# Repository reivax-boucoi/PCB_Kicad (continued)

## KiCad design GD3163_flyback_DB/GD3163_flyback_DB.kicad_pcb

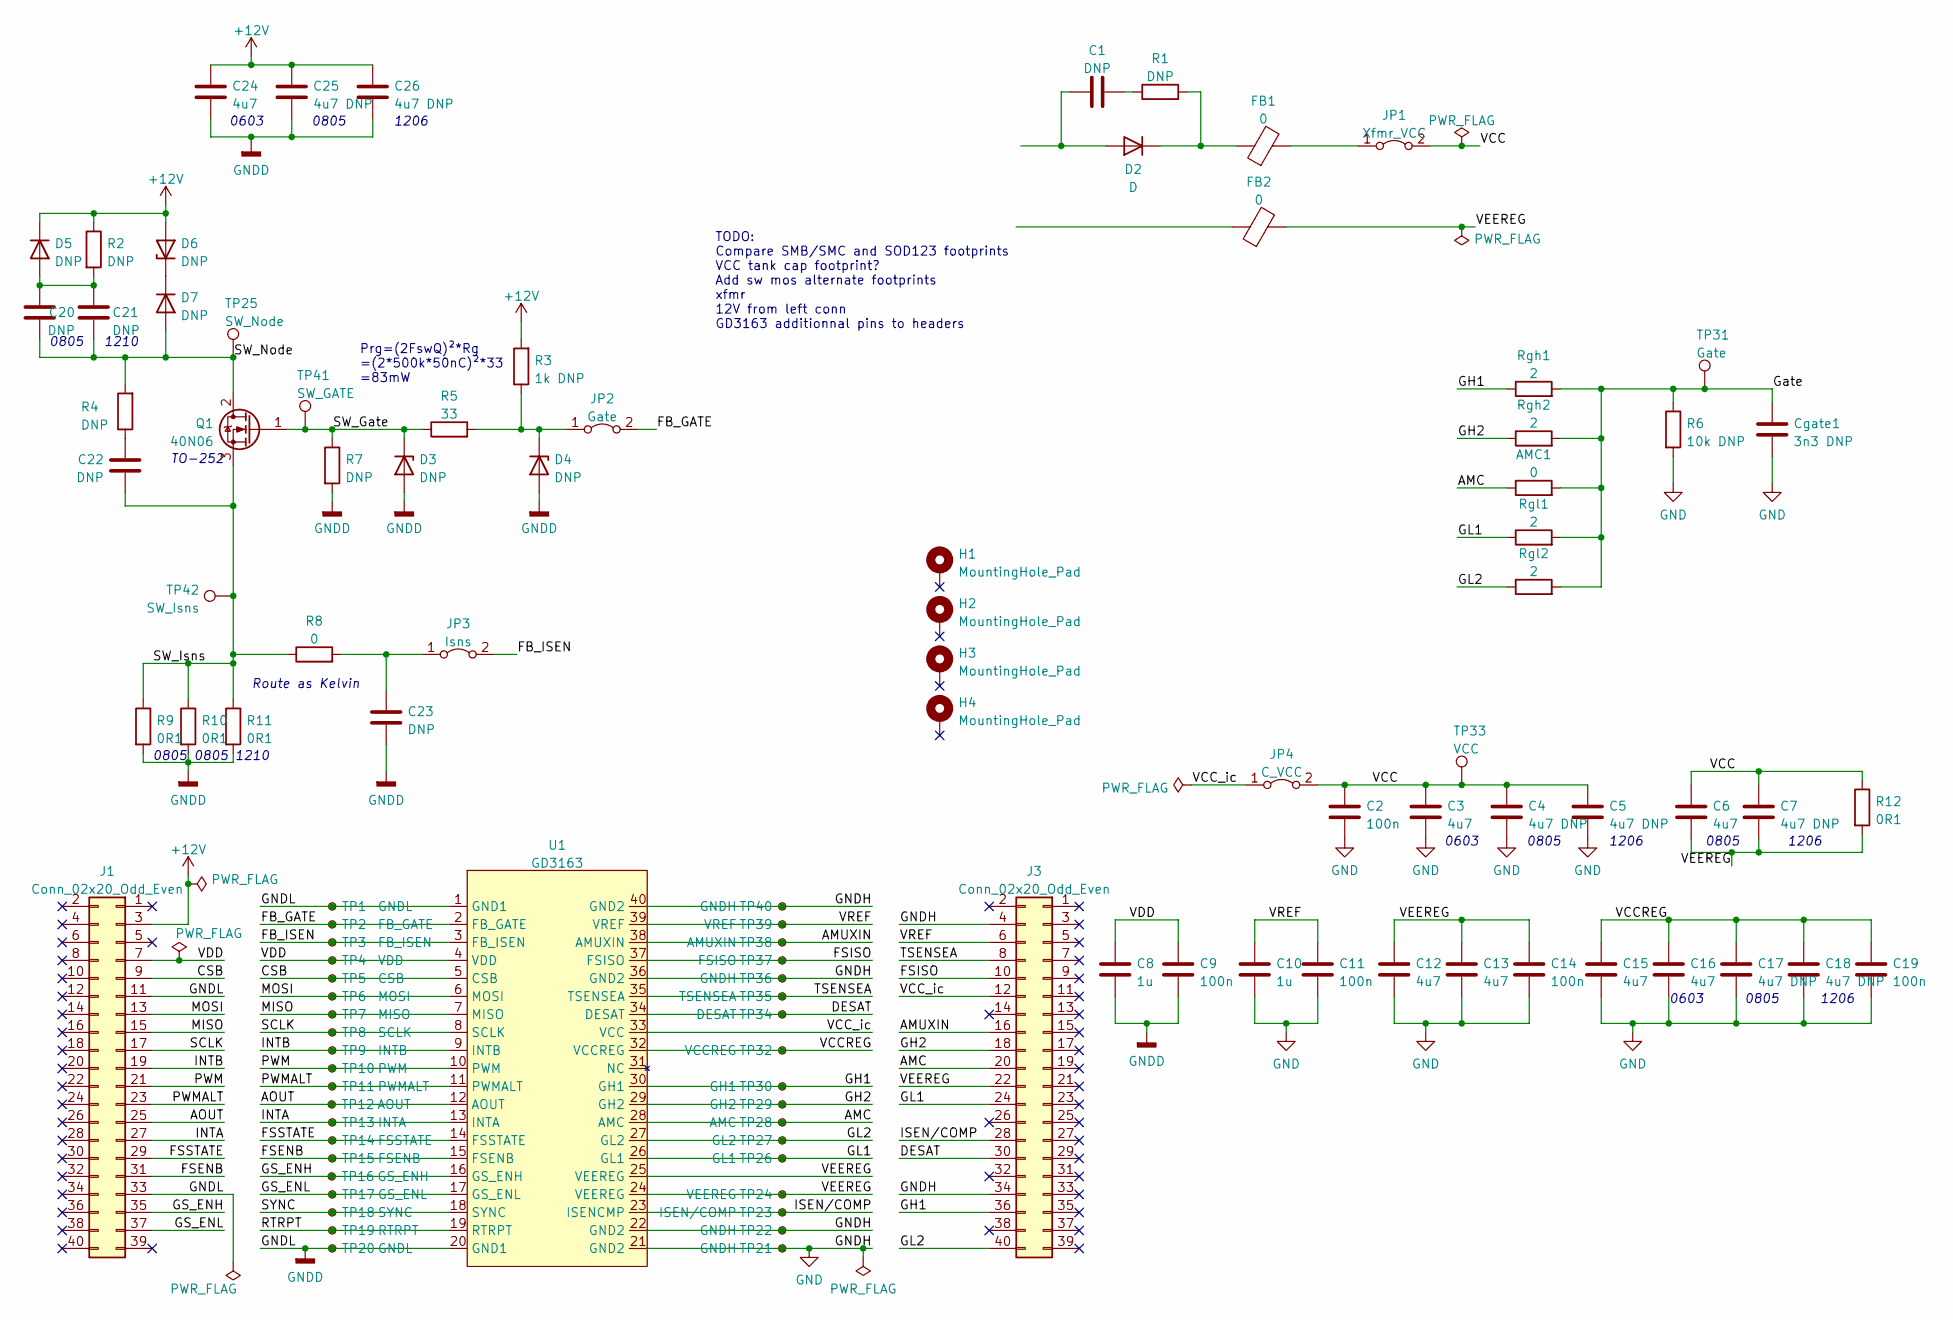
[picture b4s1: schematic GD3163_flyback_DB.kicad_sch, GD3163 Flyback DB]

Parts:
AMC1: 0; R_1206_3216Metric_Pad1.30x1.75mm_HandSolder
C1, C20, C22: DNP; C_0805_2012Metric_Pad1.18x1.45mm_HandSolder
C2, C9, C11, C14, C19: 100n; C_0603_1608Metric_Pad1.08x0.95mm_HandSolder
C3, C6, C12, C13, C15, C16, C24: 4u7; C_0603_1608Metric_Pad1.08x0.95mm_HandSolder
C4, C17, C25: 4u7 DNP; C_0805_2012Metric_Pad1.18x1.45mm_HandSolder
C5, C7, C18, C26: 4u7 DNP; C_1206_3216Metric_Pad1.33x1.80mm_HandSolder
C8, C10: 1u; C_0603_1608Metric_Pad1.08x0.95mm_HandSolder
C21: DNP; C_1210_3225Metric
C23: DNP; C_0603_1608Metric_Pad1.08x0.95mm_HandSolder
Cgate1: 3n3 DNP; C_0805_2012Metric_Pad1.18x1.45mm_HandSolder
D2: D; D_SMA-SMB_Universal_Handsoldering
D3, D4: DNP; D_SOD-323_HandSoldering
D5, D6, D7: DNP; D_SMA-SMB_Universal_Handsoldering
FB1, FB2: 0; L_0805_2012Metric_Pad1.05x1.20mm_HandSolder
H1, H2, H3, H4: MountingHole_Pad; MountingHole_4.3mm_M4_Pad_Via
J1, J3: Conn_02x20_Odd_Even; PinHeader_2x20_P2.54mm_Vertical
JP1: Xfmr_VCC; PinHeader_1x02_P2.54mm_Vertical
JP2: Gate; PinHeader_1x02_P2.54mm_Vertical
JP3: Isns; PinHeader_1x02_P2.54mm_Vertical
JP4: C_VCC; PinHeader_1x02_P2.54mm_Vertical
Q1: 40N06; TO-252-2
R1, R7: DNP; R_0805_2012Metric_Pad1.20x1.40mm_HandSolder
R2: DNP; R_1210_3225Metric_Pad1.30x2.65mm_HandSolder
R3: 1k DNP; R_0805_2012Metric_Pad1.20x1.40mm_HandSolder
R4: DNP; R_1206_3216Metric_Pad1.30x1.75mm_HandSolder
R5: 33; R_0805_2012Metric_Pad1.20x1.40mm_HandSolder
R6: 10k DNP; R_0805_2012Metric_Pad1.20x1.40mm_HandSolder
R8: 0; R_0805_2012Metric_Pad1.20x1.40mm_HandSolder
R9, R10: 0R1; R_0805_2012Metric_Pad1.20x1.40mm_HandSolder
R11: 0R1; R_1210_3225Metric_Pad1.30x2.65mm_HandSolder
R12: 0R1; R_SocketINSA_L6.3mm_D2.5mm_P10.16mm_Horizontal
Rgh1, Rgh2: 2; R_1206_3216Metric_Pad1.30x1.75mm_HandSolder
Rgl1, Rgl2: 2; R_1206_3216Metric_Pad1.30x1.75mm_HandSolder
TP1, TP20: GNDL; TestPoint_Keystone_5010-5014_Multipurpose
TP2: FB_GATE; TestPoint_Keystone_5010-5014_Multipurpose
TP3: FB_ISEN; TestPoint_Keystone_5010-5014_Multipurpose
TP4: VDD; TestPoint_Keystone_5010-5014_Multipurpose
TP5: CSB; TestPoint_Keystone_5010-5014_Multipurpose
TP6: MOSI; TestPoint_Keystone_5010-5014_Multipurpose
TP7: MISO; TestPoint_Keystone_5010-5014_Multipurpose
TP8: SCLK; TestPoint_Keystone_5010-5014_Multipurpose
TP9: INTB; TestPoint_Keystone_5010-5014_Multipurpose
TP10: PWM; TestPoint_Keystone_5010-5014_Multipurpose
TP11: PWMALT; TestPoint_Keystone_5010-5014_Multipurpose
TP12: AOUT; TestPoint_Keystone_5010-5014_Multipurpose
TP13: INTA; TestPoint_Keystone_5010-5014_Multipurpose
TP14: FSSTATE; TestPoint_Keystone_5010-5014_Multipurpose
TP15: FSENB; TestPoint_Keystone_5010-5014_Multipurpose
TP16: GS_ENH; TestPoint_Keystone_5010-5014_Multipurpose
TP17: GS_ENL; TestPoint_Keystone_5010-5014_Multipurpose
TP18: SYNC; TestPoint_Keystone_5010-5014_Multipurpose
TP19: RTRPT; TestPoint_Keystone_5010-5014_Multipurpose
TP21, TP22, TP36, TP40: GNDH; TestPoint_Keystone_5010-5014_Multipurpose
TP23: ISEN/COMP; TestPoint_Keystone_5010-5014_Multipurpose
TP24: VEEREG; TestPoint_Keystone_5010-5014_Multipurpose
TP25: SW_Node; TestPoint_Keystone_5010-5014_Multipurpose
TP26: GL1; TestPoint_Keystone_5010-5014_Multipurpose
TP27: GL2; TestPoint_Keystone_5010-5014_Multipurpose
TP28: AMC; TestPoint_Keystone_5010-5014_Multipurpose
TP29: GH2; TestPoint_Keystone_5010-5014_Multipurpose
TP30: GH1; TestPoint_Keystone_5010-5014_Multipurpose
TP31: Gate; TestPoint_Keystone_5010-5014_Multipurpose
TP32: VCCREG; TestPoint_Keystone_5010-5014_Multipurpose
TP33: VCC; TestPoint_Keystone_5010-5014_Multipurpose
TP34: DESAT; TestPoint_Keystone_5010-5014_Multipurpose
TP35: TSENSEA; TestPoint_Keystone_5010-5014_Multipurpose
TP37: FSISO; TestPoint_Keystone_5010-5014_Multipurpose
TP38: AMUXIN; TestPoint_Keystone_5010-5014_Multipurpose
TP39: VREF; TestPoint_Keystone_5010-5014_Multipurpose
TP41: SW_GATE; TestPoint_Keystone_5010-5014_Multipurpose
TP42: SW_Isns; TestPoint_Keystone_5010-5014_Multipurpose
U1: GD3163; GD3163_SOIC-40_1.575x0.3, 9.575w

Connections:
+12V: C24.1, C25.1, C26.1, D5.1 (K), D6.2 (A), J1.3, R2.1, R3.2
/AMC: AMC1.1, J3.20, TP28.1, U1.28 (AMC)
/AMUXIN: J3.16, TP38.1, U1.38 (AMUXIN)
/AOUT: J1.25, TP12.1, U1.12 (AOUT)
/CSB: J1.9, TP5.1, U1.5 (CSB)
/DESAT: J3.30, TP34.1, U1.34 (DESAT)
/FB_GATE: JP2.2 (B), TP2.1, U1.2 (FB_GATE)
/FB_ISEN: JP3.2 (B), TP3.1, U1.3 (FB_ISEN)
/FSENB: J1.31, TP15.1, U1.15 (FSENB)
/FSISO: J3.10, TP37.1, U1.37 (FSISO)
/FSSTATE: J1.29, TP14.1, U1.14 (FSSTATE)
/GH1: J3.36, Rgh1.1, TP30.1, U1.30 (GH1)
/GH2: J3.18, Rgh2.1, TP29.1, U1.29 (GH2)
/GL1: J3.24, Rgl1.1, TP26.1, U1.26 (GL1)
/GL2: J3.40, Rgl2.1, TP27.1, U1.27 (GL2)
/GS_ENH: J1.35, TP16.1, U1.16 (GS_ENH)
/GS_ENL: J1.37, TP17.1, U1.17 (GS_ENL)
/Gate: AMC1.2, Cgate1.1, R6.1, Rgh1.2, Rgh2.2, Rgl1.2, Rgl2.2, TP31.1
/INTA: J1.27, TP13.1, U1.13 (INTA)
/INTB: J1.19, TP9.1, U1.9 (INTB)
/ISEN/COMP: J3.28, TP23.1, U1.23 (ISENCMP)
/MISO: J1.15, TP7.1, U1.7 (MISO)
/MOSI: J1.13, TP6.1, U1.6 (MOSI)
/PWM: J1.21, TP10.1, U1.10 (PWM)
/PWMALT: J1.23, TP11.1, U1.11 (PWMALT)
/RTRPT: TP19.1, U1.19 (RTRPT)
/SCLK: J1.17, TP8.1, U1.8 (SCLK)
/SW_Gate: D3.1 (K), Q1.1 (G), R5.1, R7.1, TP41.1
/SW_Isns: C22.2, Q1.3 (S), R8.1, R9.1, R10.1, R11.1, TP42.1
/SW_Node: C20.2, C21.2, D7.2 (A), Q1.2 (D), R4.2, TP25.1
/SYNC: TP18.1, U1.18 (SYNC)
/TSENSEA: J3.8, TP35.1, U1.35 (TSENSEA)
/VCC: C2.1, C3.1, C4.1, C5.1, C6.1, C7.1, JP1.2 (B), JP4.2 (B), R12.1, TP33.1
/VCCREG: C15.1, C16.1, C17.1, C18.1, C19.1, TP32.1, U1.32 (VCCREG)
/VCC_ic: J3.12, JP4.1 (A), U1.33 (VCC)
/VDD: C8.1, C9.1, J1.7, TP4.1, U1.4 (VDD)
/VEEREG: C6.2, C7.2, C12.1, C13.1, C14.1, FB2.2, J3.22, R12.2, TP24.1, U1.24 (VEEREG), U1.25 (VEEREG)
/VREF: C10.1, C11.1, J3.6, TP39.1, U1.39 (VREF)
GND: C2.2, C3.2, C4.2, C5.2, C10.2, C11.2, C12.2, C13.2, C14.2, C15.2, C16.2, C17.2, C18.2, C19.2, Cgate1.2, J3.4, J3.34, R6.2, TP21.1, TP22.1, TP36.1, TP40.1, U1.21 (GND2), U1.22 (GND2), U1.36 (GND2), U1.40 (GND2)
GNDD: C8.2, C9.2, C23.2, C24.2, C25.2, C26.2, D3.2 (A), D4.2 (A), J1.11, J1.33, R7.2, R9.2, R10.2, R11.2, TP1.1, TP20.1, U1.1 (GND1), U1.20 (GND1)
unnamed: C1.1, D2.2 (A)
unnamed: C1.2, R1.1
unnamed: C20.1, C21.1, D5.2 (A), R2.2
unnamed: C22.1, R4.1
unnamed: C23.1, JP3.1 (A), R8.2
unnamed: D2.1 (K), FB1.1, R1.2
unnamed: D4.1 (K), JP2.1 (A), R3.1, R5.2
unnamed: D6.1 (K), D7.1 (K)
unnamed: FB1.2, JP1.1 (A)

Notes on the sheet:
0805 1210
0805 1206
0603 0805 1206
0805 0805 1210
TO-252
TODO: Compare SMB/SMC and SOD123 footprints VCC tank cap footprint? Add sw mos alternate footprints xfmr 12V from left conn GD3163 additionnal pins to headers
0603 0805 1206
Prg=(2FswQ)²*Rg =(2*500k*50nC)²*33 =83mW
Route as Kelvin

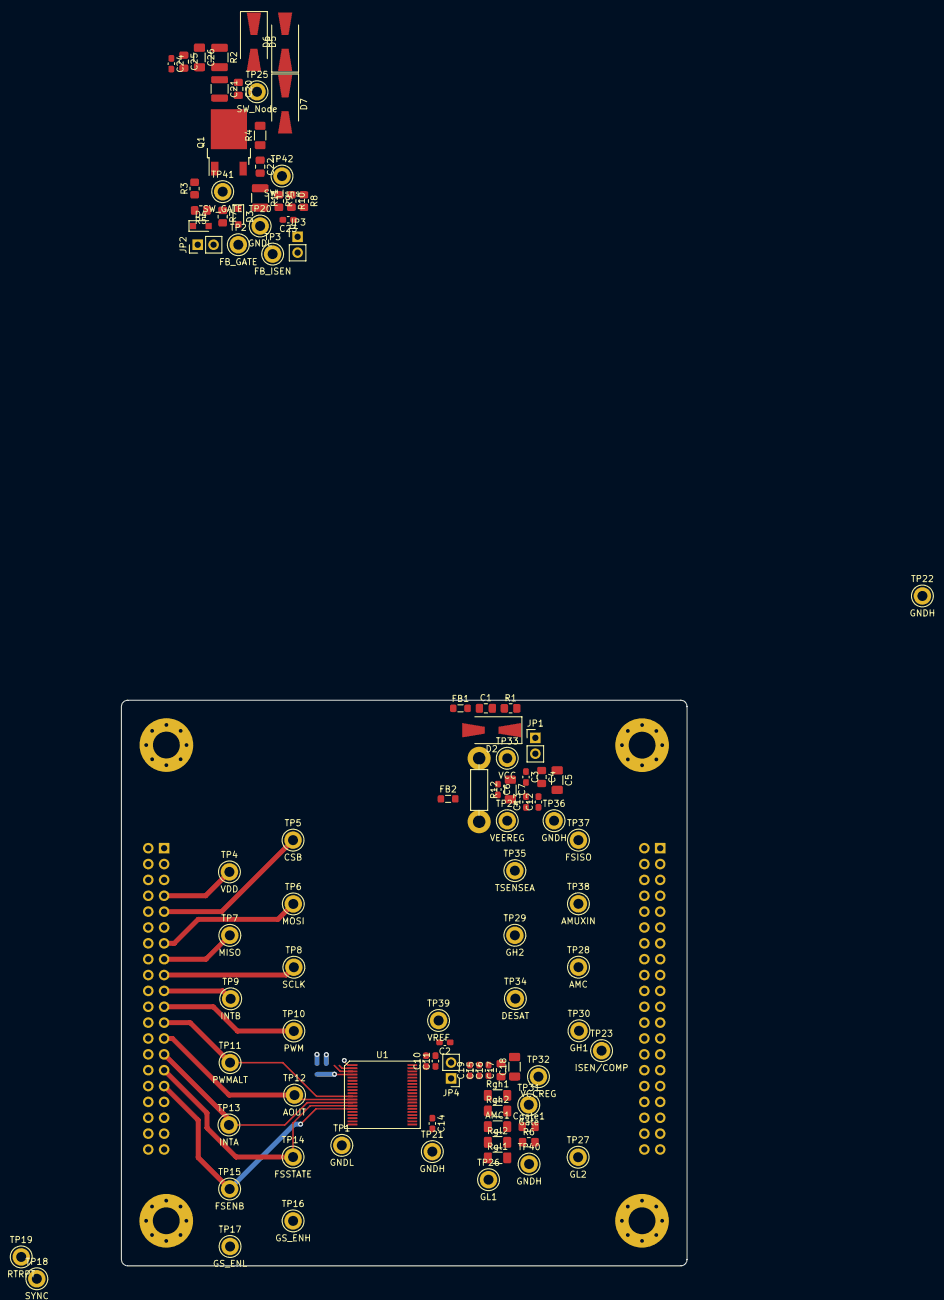
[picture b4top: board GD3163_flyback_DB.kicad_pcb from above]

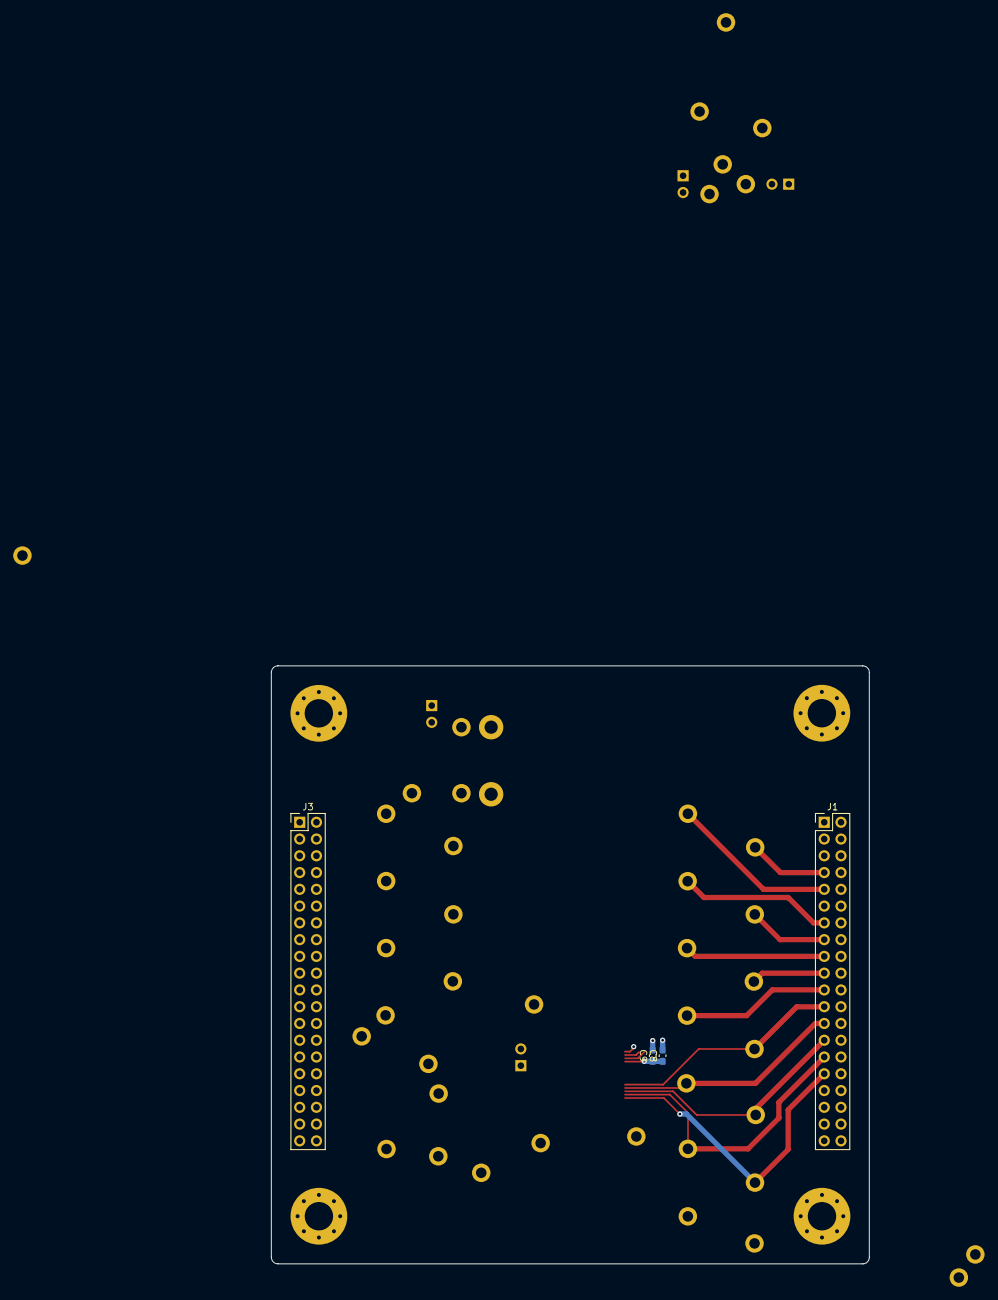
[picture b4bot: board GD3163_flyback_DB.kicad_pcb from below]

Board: 4 copper layers, 90.6 x 90.6 mm, 106 parts (4 on the bottom side), 49 nets.

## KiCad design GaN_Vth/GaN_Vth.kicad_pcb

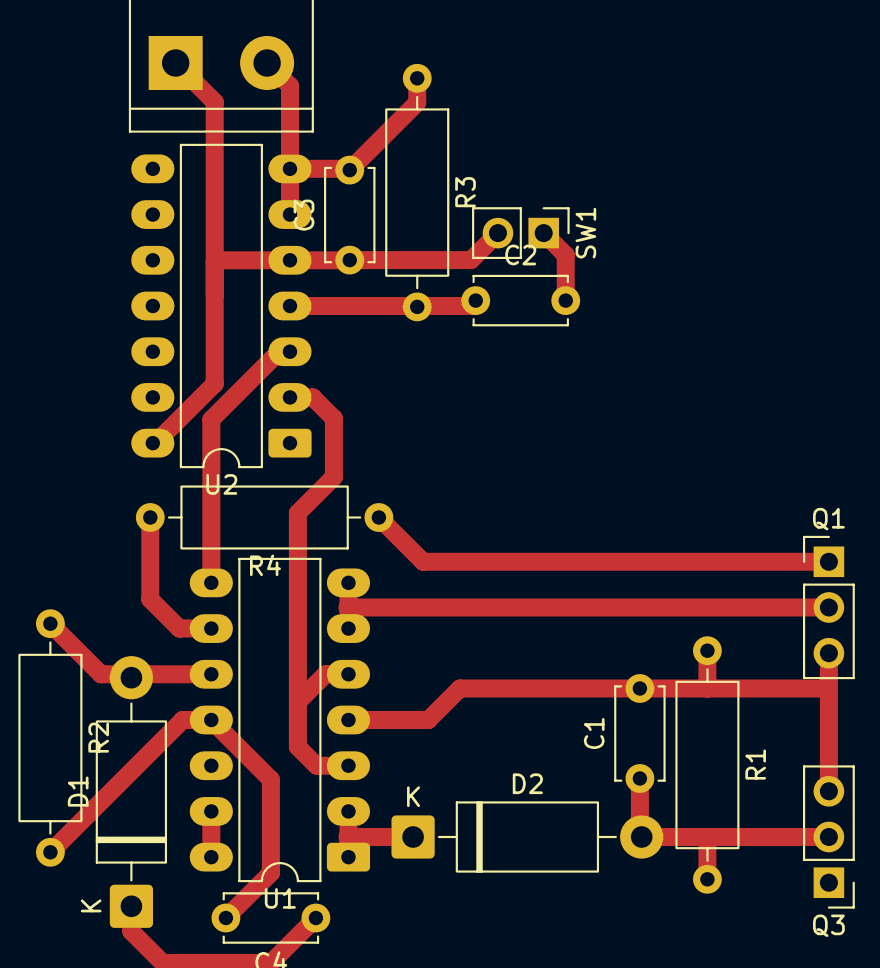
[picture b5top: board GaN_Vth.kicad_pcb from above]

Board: 2 copper layers, 16 parts (0 on the bottom side), 13 nets.

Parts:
C1: C; C_Disc_D5.0mm_W2.5mm_P5.00mm
C2: 1n; C_Disc_D5.0mm_W2.5mm_P5.00mm
C3, C4: 100n; C_Disc_D5.0mm_W2.5mm_P5.00mm
D1: 3V3; D_DO-15_P12.70mm_Horizontal
D2: D_Schottky; D_DO-15_P12.70mm_Horizontal
J1: Screw_Terminal_01x02; TerminalBlock_bornier-2_P5.08mm
Q1: PMOS; PinHeader_1x03_P2.54mm_Vertical
Q3: GS66502B; PinHeader_1x03_P2.54mm_Vertical
R1: R; R_Axial_DIN0309_L9.0mm_D3.2mm_P12.70mm_Horizontal
R2, R3, R4: 10k; R_Axial_DIN0309_L9.0mm_D3.2mm_P12.70mm_Horizontal
SW1: SW_SPST; PinHeader_1x02_P2.54mm_Vertical
U1: LM324; DIP-14_W7.62mm_LongPads
U2: 4013; DIP-14_W7.62mm_LongPads

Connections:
+15V: C1.2, C3.1, C4.1, D1.1 (K), J1.1, Q1.3 (S), Q3.3 (S), R1.1, SW1.2 (B), U1.4 (V+), U2.5 (D), U2.14 (VDD)
/DC-: Q1.1 (D), R4.1
GND: C3.2, C4.2, J1.2, R2.2, R3.1, U1.11 (V-), U2.6 (S), U2.7 (VSS)
unnamed: D1.2 (A), R2.1, U1.10 (+)
unnamed: C1.1, D2.2 (A), Q3.2 (G), R1.2
unnamed: D2.1 (K), U1.1, U1.2 (-)
unnamed: Q1.2 (G), U1.6 (-), U1.7
unnamed: C2.2, SW1.1 (A)
unnamed: U1.3 (+), U1.5 (+), U2.2 (~Q)
unnamed: R4.2, U1.9 (-)
unnamed: U1.13 (-), U1.14
unnamed: U1.8, U2.3 (C)
unnamed: C2.1, R3.2, U2.4 (R)

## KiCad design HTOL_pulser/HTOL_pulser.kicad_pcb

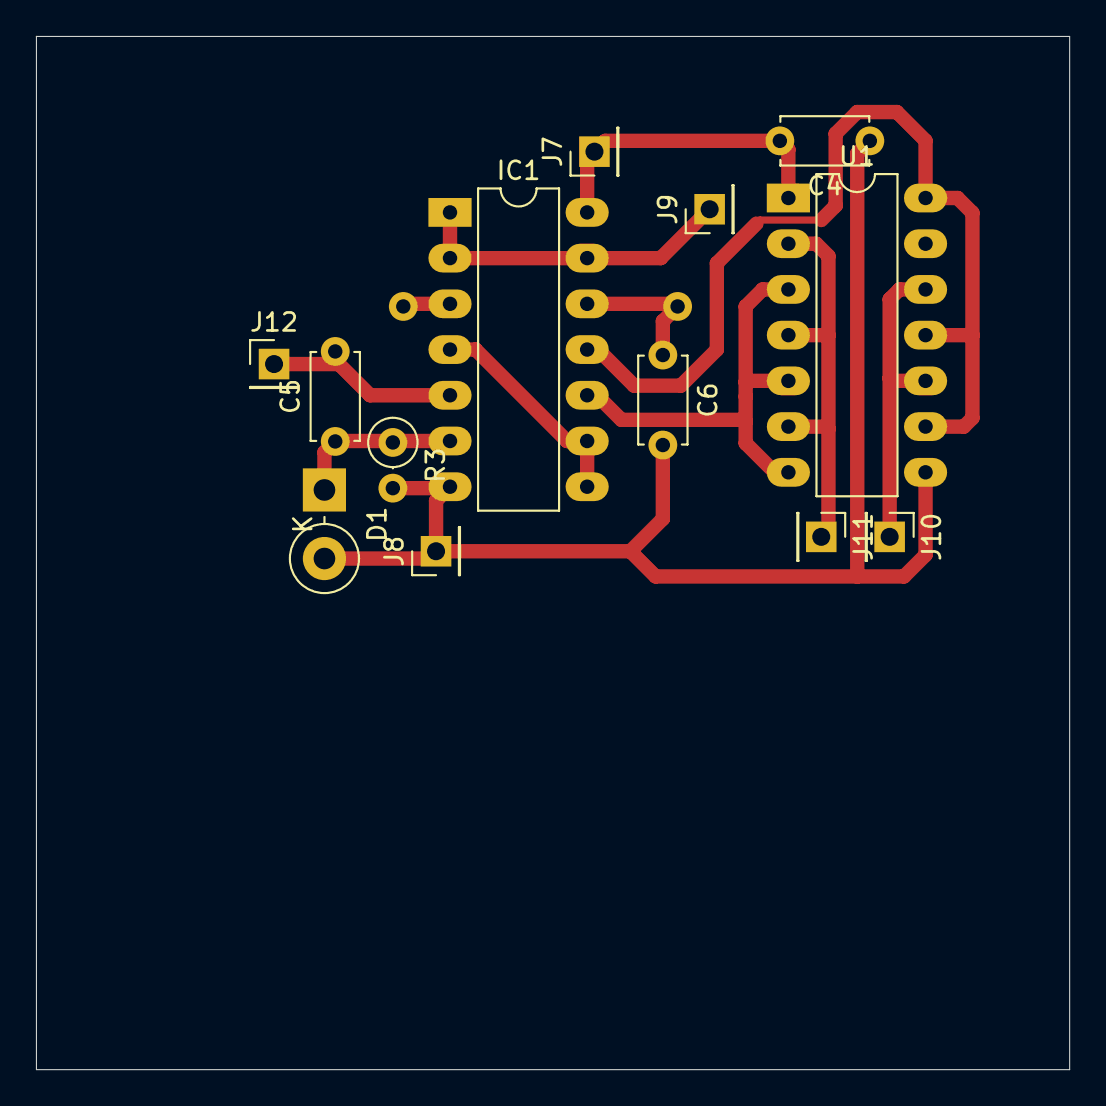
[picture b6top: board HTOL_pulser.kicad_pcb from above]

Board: 2 copper layers, 57.4 x 57.4 mm, 14 parts (1 on the bottom side), 12 nets.

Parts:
C4: 100n; C_Disc_D4.7mm_W2.5mm_P5.00mm
C5, C6: 68p; C_Disc_D4.7mm_W2.5mm_P5.00mm
D1: D_Schottky; D_DO-15_P3.81mm_Vertical_KathodeUp
IC1: 4093D; DIP-14_W7.62mm_LongPads
J7: +5V; PinHeader_1x01_P2.54mm_Vertical
J8: GND; PinHeader_1x01_P2.54mm_Vertical
J9: IN_OFF; PinHeader_1x01_P2.54mm_Vertical
J10: OUT_OFF; PinHeader_1x01_P2.54mm_Vertical
J11: OUT_ON; PinHeader_1x01_P2.54mm_Vertical
J12: IN_ON; PinHeader_1x01_P2.54mm_Vertical
R3: 10k; R_Axial_DIN0207_L6.3mm_D2.5mm_P2.54mm_Vertical
R4: 10k; R_Axial_DIN0207_L6.3mm_D2.5mm_P15.24mm_Horizontal
U1: 4050; DIP-14_W7.62mm_LongPads

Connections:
+5V: C4.2, IC1.14 (VDD), J7.1, U1.1 (VCC)
GND: C4.1, C6.2, D1.2 (A), IC1.7 (VSS), J8.1, R3.2, U1.8 (VSS)
unnamed: C5.1, D1.1 (K), IC1.6 (I1), R3.1
unnamed: IC1.1 (I0), IC1.2 (I1), IC1.13 (I1), J9.1
unnamed: IC1.3 (O), R4.1
unnamed: C5.2, IC1.5 (I0), J12.1
unnamed: IC1.4 (O), IC1.8 (I0), IC1.9 (I1)
unnamed: IC1.10 (O), U1.3, U1.5, U1.7
unnamed: C6.1, IC1.12 (I0), R4.2
unnamed: IC1.11 (O), U1.9, U1.11, U1.14
unnamed: J10.1, U1.10, U1.12
unnamed: J11.1, U1.2, U1.4, U1.6

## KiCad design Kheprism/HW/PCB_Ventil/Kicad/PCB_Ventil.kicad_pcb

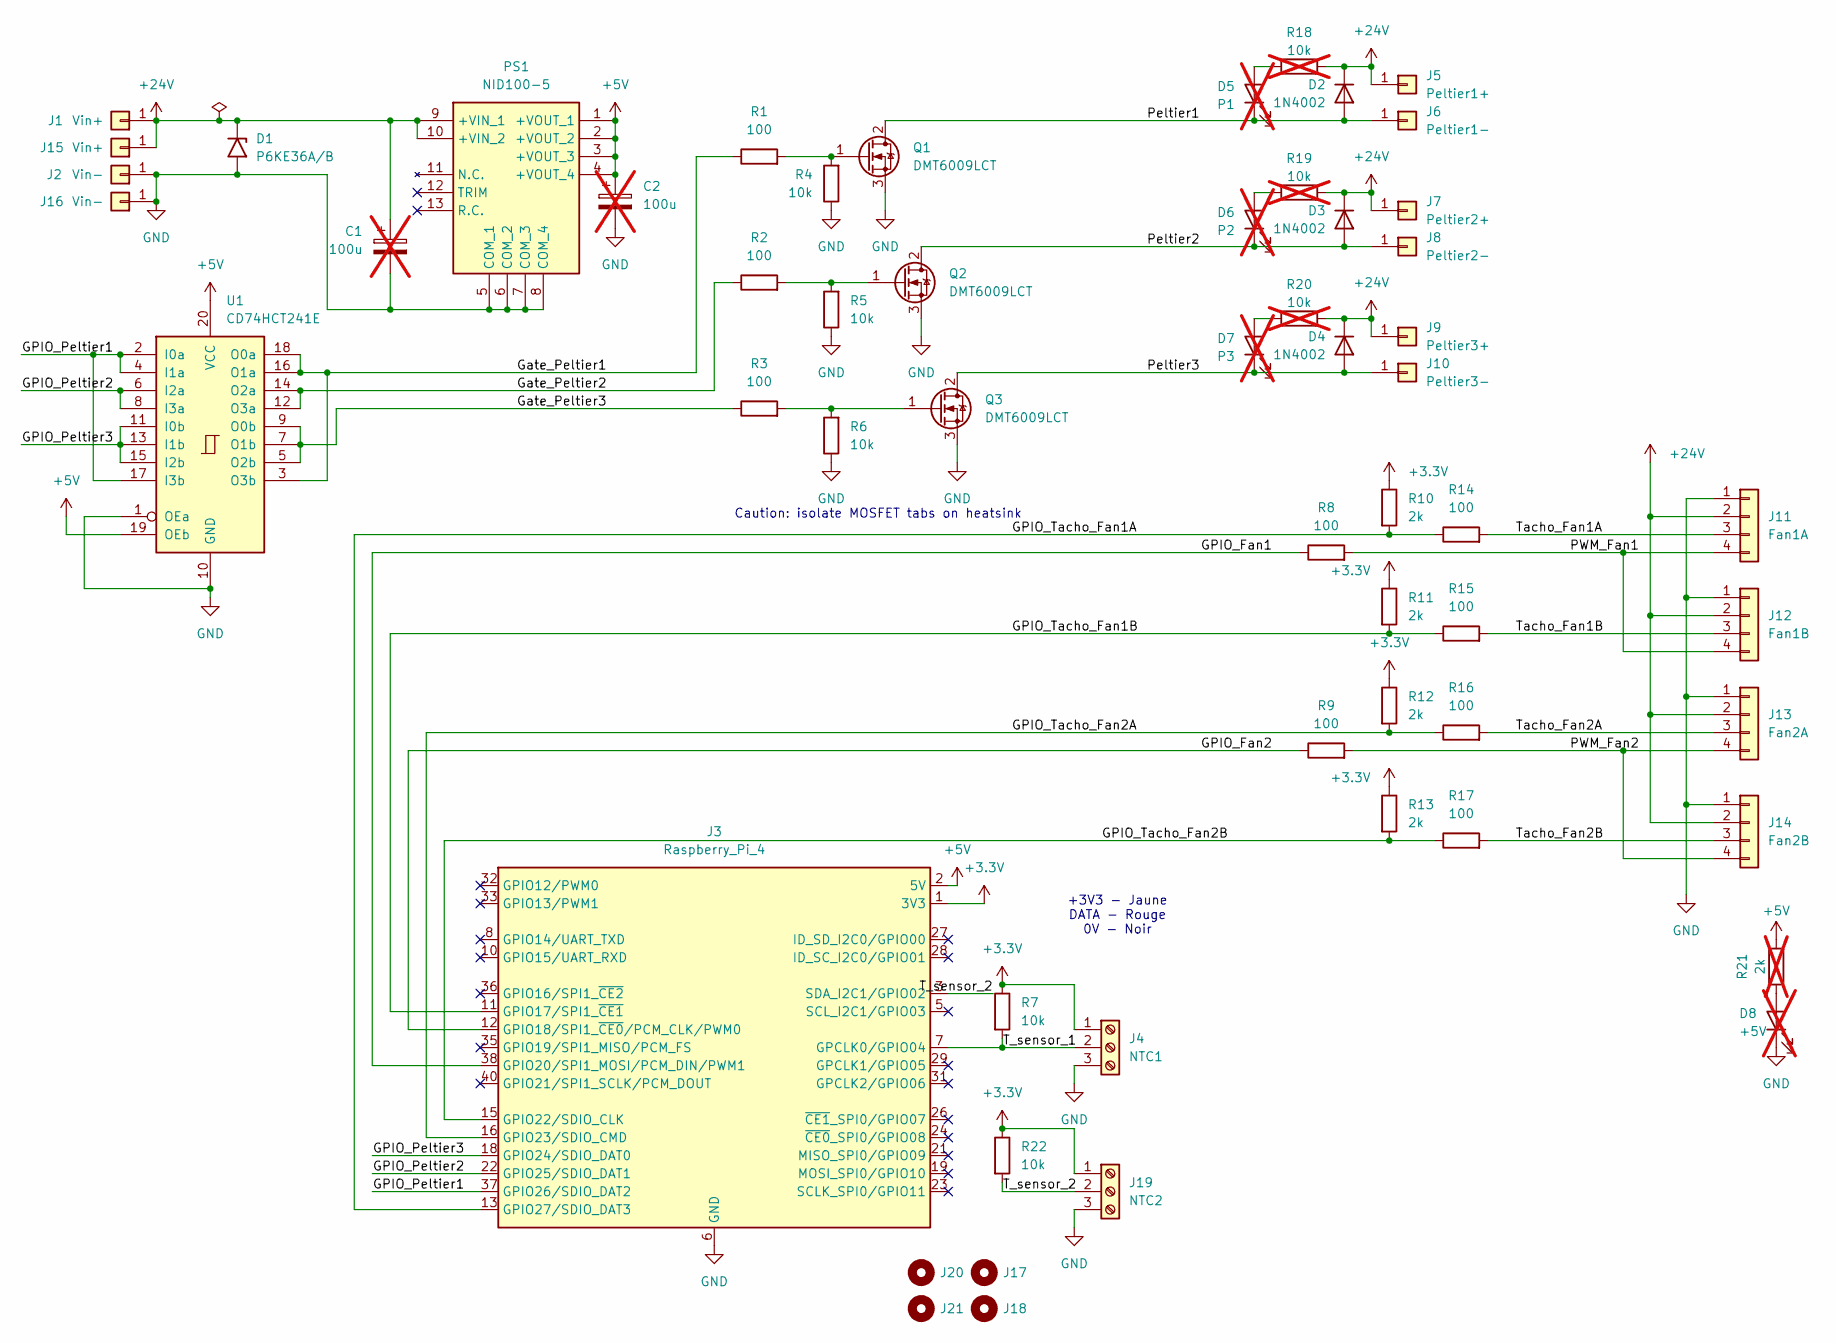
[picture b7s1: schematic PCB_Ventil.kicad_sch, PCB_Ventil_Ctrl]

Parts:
C1, C2: 100u; CP_Radial_D10.0mm_P2.50mm_P5.00mm; not fitted
D1: P6KE36A/B; D_DO-201AE_P15.24mm_Horizontal; Farnell Part Number P6KE36A/B
D2, D3, D4: 1N4002; D_DO-41_SOD81_P10.16mm_Horizontal; Farnell Part Number 1N4002-G
D5: P1; LED_D5.0mm; Farnell Part Number BL-B5134-1-TBS20A; not fitted
D6: P2; LED_D5.0mm; Farnell Part Number BL-B5134-1-TBS20A; not fitted
D7: P3; LED_D5.0mm; Farnell Part Number BL-B5134-1-TBS20A; not fitted
D8: +5V; LED_D5.0mm; Farnell Part Number BL-B5134-1-TBS20A; not fitted
J1, J15: Vin+; Faston_1287-250mils_P5.08mm; Farnell Part Number 4966
J2, J16: Vin-; Faston_1287-250mils_P5.08mm; Farnell Part Number 4966
J3: Raspberry_Pi_4; PinSocket_2x20_P2.54mm_Vertical; Farnell Part Number 61304021821
J4: NTC1; TerminalBlock_MaiXu_MX126-5.0-03P_1x03_P5.00mm; Farnell Part Number BLR513-5-V
J5: Peltier1+; Faston_1287-250mils_P5.08mm; Farnell Part Number 4966
J6: Peltier1-; Faston_1287-250mils_P5.08mm; Farnell Part Number 4966
J7: Peltier2+; Faston_1287-250mils_P5.08mm; Farnell Part Number 4966
J8: Peltier2-; Faston_1287-250mils_P5.08mm; Farnell Part Number 4966
J9: Peltier3+; Faston_1287-250mils_P5.08mm; Farnell Part Number 4966
J10: Peltier3-; Faston_1287-250mils_P5.08mm; Farnell Part Number 4966
J11: Fan1A; FanPinHeader_1x04_P2.54mm_Vertical; Farnell Part Number 0470531000
J12: Fan1B; FanPinHeader_1x04_P2.54mm_Vertical; Farnell Part Number 0470531000
J13: Fan2A; FanPinHeader_1x04_P2.54mm_Vertical; Farnell Part Number 0470531000
J14: Fan2B; FanPinHeader_1x04_P2.54mm_Vertical; Farnell Part Number 0470531000
J17, J18, J20, J21: Peltier1+; MountingHole_3.2mm_M3; Farnell Part Number 4966
J19: NTC2; TerminalBlock_MaiXu_MX126-5.0-03P_1x03_P5.00mm; Farnell Part Number BLR513-5-V
PS1: NID100-5; NID1005; Manufacturer_Part_Number NID100-5; Farnell Part Number NID100-5
Q1, Q2, Q3: DMT6009LCT; TO-220-3_Vertical; Farnell Part Number DMT6009LCT
R1, R2, R9, R16: 100; R_Axial_DIN0309_L9.0mm_D3.2mm_P2.54mm_Vertical; Farnell Price/Stock 0.0217
R3, R8, R14, R15, R17: 100; R_Axial_DIN0309_L9.0mm_D3.2mm_P12.70mm_Horizontal; Farnell Price/Stock 0.0217
R4, R5, R6, R7, R22: 10k; R_Axial_DIN0309_L9.0mm_D3.2mm_P2.54mm_Vertical; Farnell Price/Stock 0
R10, R11, R12, R13: 2k; R_Axial_DIN0309_L9.0mm_D3.2mm_P2.54mm_Vertical; Farnell Price/Stock 0
R18, R19, R20: 10k; R_Axial_DIN0309_L9.0mm_D3.2mm_P2.54mm_Vertical; Farnell Price/Stock 0; not fitted
R21: 2k; R_Axial_DIN0309_L9.0mm_D3.2mm_P2.54mm_Vertical; Farnell Price/Stock 0; not fitted
U1: CD74HCT241E; DIP-20_W7.62mm_LongPads

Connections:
+3.3V: J3.1 (3V3), J3.17 (3V3), J4.1, J19.1, R7.1, R10.1, R11.1, R12.1, R13.1, R22.1
+5V: C2.1, J3.2 (5V), J3.4 (5V), PS1.1 (+VOUT_1), PS1.2 (+VOUT_2), PS1.3 (+VOUT_3), PS1.4 (+VOUT_4), R21.1, U1.19 (OEb), U1.20 (VCC)
+24V: C1.1, D1.1 (A1), D2.1 (K), D3.1 (K), D4.1 (K), J1.1, J5.1, J7.1, J9.1, J11.2, J12.2, J13.2, J14.2, J15.1, PS1.9 (+VIN_1), PS1.10 (+VIN_2), R18.1, R19.1, R20.1
/GPIO_Fan1: J3.38 (GPIO20/SPI1_MOSI/PCM_DIN/PWM1), R8.1
/GPIO_Fan2: J3.12 (GPIO18/SPI1_~CE0/PCM_CLK/PWM0), R9.1
/GPIO_Peltier1: J3.37 (GPIO26/SDIO_DAT2), U1.2 (I0a), U1.4 (I1a), U1.17 (I3b)
/GPIO_Peltier2: J3.22 (GPIO25/SDIO_DAT1), U1.6 (I2a), U1.8 (I3a)
/GPIO_Peltier3: J3.18 (GPIO24/SDIO_DAT0), U1.11 (I0b), U1.13 (I1b), U1.15 (I2b)
/GPIO_Tacho_Fan1A: J3.13 (GPIO27/SDIO_DAT3), R10.2, R14.1
/GPIO_Tacho_Fan1B: J3.11 (GPIO17/SPI1_~CE1), R11.2, R15.1
/GPIO_Tacho_Fan2A: J3.16 (GPIO23/SDIO_CMD), R12.2, R16.1
/GPIO_Tacho_Fan2B: J3.15 (GPIO22/SDIO_CLK), R13.2, R17.1
/Gate_Peltier1: R1.1, U1.3 (O3b), U1.16 (O1a), U1.18 (O0a)
/Gate_Peltier2: R2.1, U1.12 (O3a), U1.14 (O2a)
/Gate_Peltier3: R3.1, U1.5 (O2b), U1.7 (O1b), U1.9 (O0b)
/PWM_Fan1: J11.4, J12.4, R8.2
/PWM_Fan2: J13.4, J14.4, R9.2
/Peltier1: D2.2 (A), D5.1 (K), J6.1, Q1.2 (D)
/Peltier2: D3.2 (A), D6.1 (K), J8.1, Q2.2 (D)
/Peltier3: D4.2 (A), D7.1 (K), J10.1, Q3.2 (D)
/T_sensor_1: J3.7 (GPCLK0/GPIO04), J4.2, R7.2
/T_sensor_2: J3.3 (SDA_I2C1/GPIO02), J19.2, R22.2
/Tacho_Fan1A: J11.3, R14.2
/Tacho_Fan1B: J12.3, R15.2
/Tacho_Fan2A: J13.3, R16.2
/Tacho_Fan2B: J14.3, R17.2
GND: C1.2, C2.2, D1.2 (A2), D8.1 (K), J2.1, J3.6 (GND), J3.9 (GND), J3.14 (GND), J3.20 (GND), J3.25 (GND), J3.30 (GND), J3.34 (GND), J3.39 (GND), J4.3, J11.1, J12.1, J13.1, J14.1, J16.1, J19.3, PS1.5 (COM_1), PS1.6 (COM_2), PS1.7 (COM_3), PS1.8 (COM_4), Q1.3 (S), Q2.3 (S), Q3.3 (S), R4.1, R5.1, R6.1, U1.1 (OEa), U1.10 (GND)
unnamed: D5.2 (A), R18.2
unnamed: D6.2 (A), R19.2
unnamed: D7.2 (A), R20.2
unnamed: D8.2 (A), R21.2
unnamed: Q1.1 (G), R1.2, R4.2
unnamed: Q2.1 (G), R2.2, R5.2
unnamed: Q3.1 (G), R3.2, R6.2

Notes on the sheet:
Caution: isolate MOSFET tabs on heatsink
+3V3 - Jaune DATA - Rouge 0V - Noir

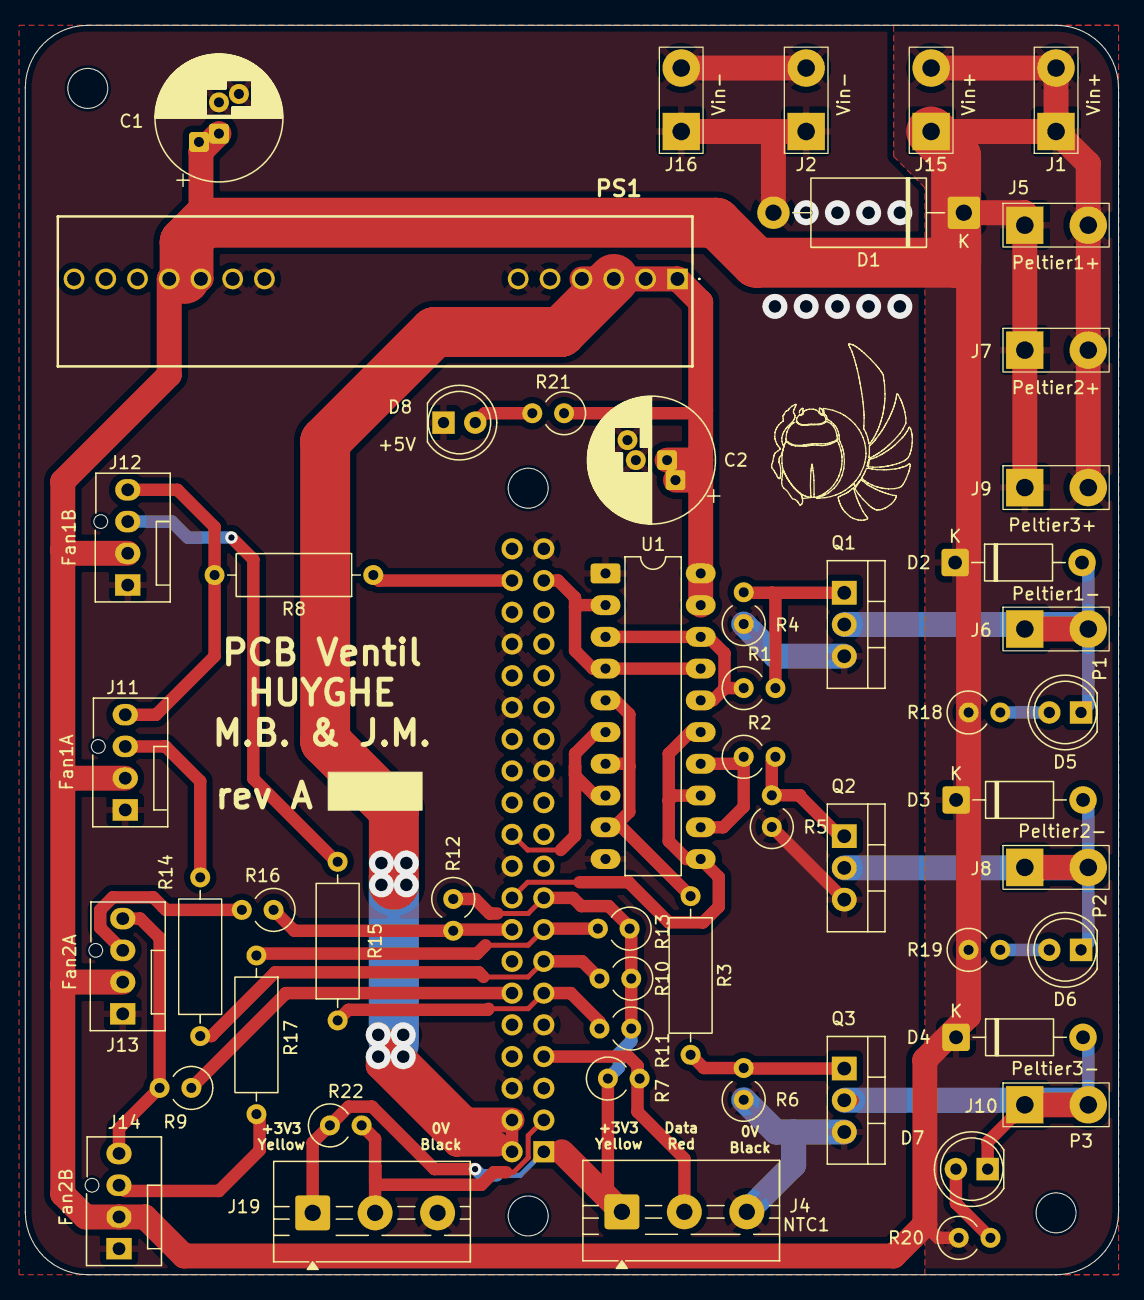
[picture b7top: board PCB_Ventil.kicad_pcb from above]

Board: 2 copper layers, 87.5 x 100.0 mm, 58 parts (1 on the bottom side), 34 nets.

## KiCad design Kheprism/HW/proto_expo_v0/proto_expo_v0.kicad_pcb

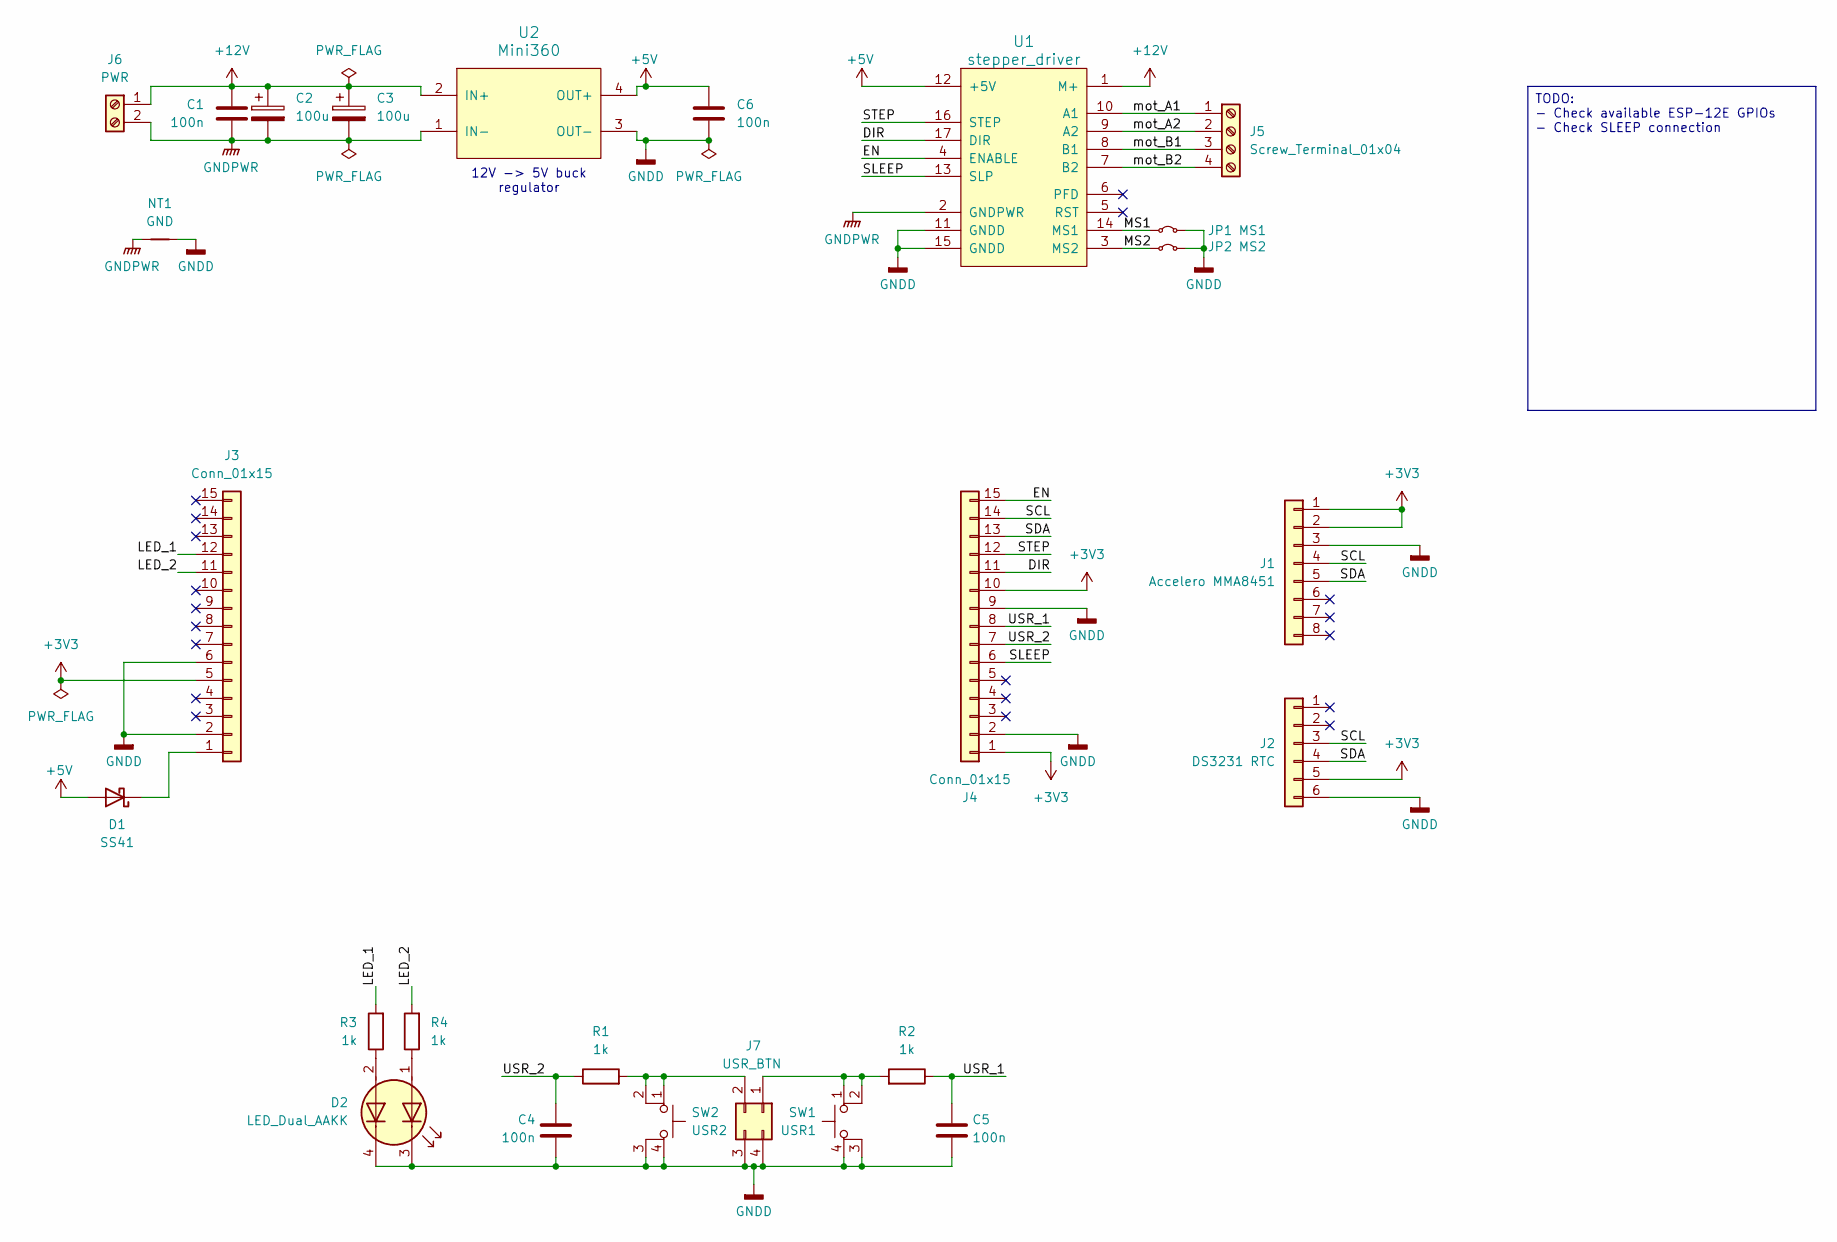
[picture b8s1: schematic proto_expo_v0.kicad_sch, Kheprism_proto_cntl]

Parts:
C1, C4, C5, C6: 100n; C_0805_2012Metric_Pad1.18x1.45mm_HandSolder
C2, C3: 100u; CP_Radial_D10.0mm_P2.50mm_P5.00mm
D1: SS41; D_SMB
D2: LED_Dual_AAKK; LED_Avago_PLCC4_3.2x2.8mm_CW
J1: Accelero MMA8451; PinSocket_1x08_P2.54mm_Vertical
J2: DS3231 RTC; PinSocket_1x06_P2.54mm_Vertical
J3, J4: Conn_01x15; PinSocket_1x15_P2.54mm_Vertical
J5: Screw_Terminal_01x04; TerminalBlock_bornier-4_P5.08mm
J6: PWR; TerminalBlock_bornier-2_P5.08mm
J7: USR_BTN; PinHeader_2x02_P2.00mm_Vertical
JP1: MS1; SolderJumper-2_P1.3mm_Bridged_RoundedPad1.0x1.5mm
JP2: MS2; SolderJumper-2_P1.3mm_Bridged_RoundedPad1.0x1.5mm
NT1: GND; NetTie-2_SMD_Pad0.5mm
R1, R2, R3, R4: 1k; R_0805_2012Metric_Pad1.20x1.40mm_HandSolder
SW1: USR1; SW_PUSH_6mm_H4.3mm
SW2: USR2; SW_PUSH_6mm_H4.3mm
U1: stepper_driver; easy_stepper_driver
U2: Mini360; Mini360_step-down

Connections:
+3V3: J1.1, J1.2, J2.5, J3.5, J4.1, J4.10
+5V: C6.1, D1.2 (A), U1.12 (+5V), U2.4 (OUT+)
+12V: C1.1, C2.1, C3.1, J6.1, U1.1 (M+), U2.2 (IN+)
/DIR: J4.11, U1.17 (DIR)
/EN: J4.15, U1.4 (ENABLE)
/LED_1: J3.12, R3.2
/LED_2: J3.11, R4.2
/MS1: JP1.1 (A), U1.14 (MS1)
/MS2: JP2.1 (A), U1.3 (MS2)
/SCL: J1.4, J2.3, J4.14
/SDA: J1.5, J2.4, J4.13
/SLEEP: J4.6, U1.13 (SLP)
/STEP: J4.12, U1.16 (STEP)
/USR_1: C5.1, J4.8, R2.1
/USR_2: C4.1, J4.7, R1.1
/mot_A1: J5.1, U1.10 (A1)
/mot_A2: J5.2, U1.9 (A2)
/mot_B1: J5.3, U1.8 (B1)
/mot_B2: J5.4, U1.7 (B2)
GNDD: C4.2, C5.2, C6.2, D2.3 (K1), D2.4 (K2), J1.3, J2.6, J3.2, J3.6, J4.2, J4.9, J7.3, J7.4, JP1.2 (B), JP2.2 (B), NT1.2, SW1.3 (K), SW1.4 (A), SW2.3 (K), SW2.4 (A), U1.11 (GNDD), U1.15 (GNDD), U2.3 (OUT-)
GNDPWR: C1.2, C2.2, C3.2, J6.2, NT1.1, U1.2 (GNDPWR), U2.1 (IN-)
unnamed: D1.1 (K), J3.1
unnamed: D2.1 (A1), R4.1
unnamed: D2.2 (A2), R3.1
unnamed: J7.1, R2.2, SW1.1, SW1.2
unnamed: J7.2, R1.2, SW2.1, SW2.2

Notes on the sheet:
12V -> 5V buck regulator
TODO: - Check available ESP-12E GPIOs - Check SLEEP connection

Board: 2 copper layers, 25 parts (0 on the bottom side), 26 nets, no tracks yet.
